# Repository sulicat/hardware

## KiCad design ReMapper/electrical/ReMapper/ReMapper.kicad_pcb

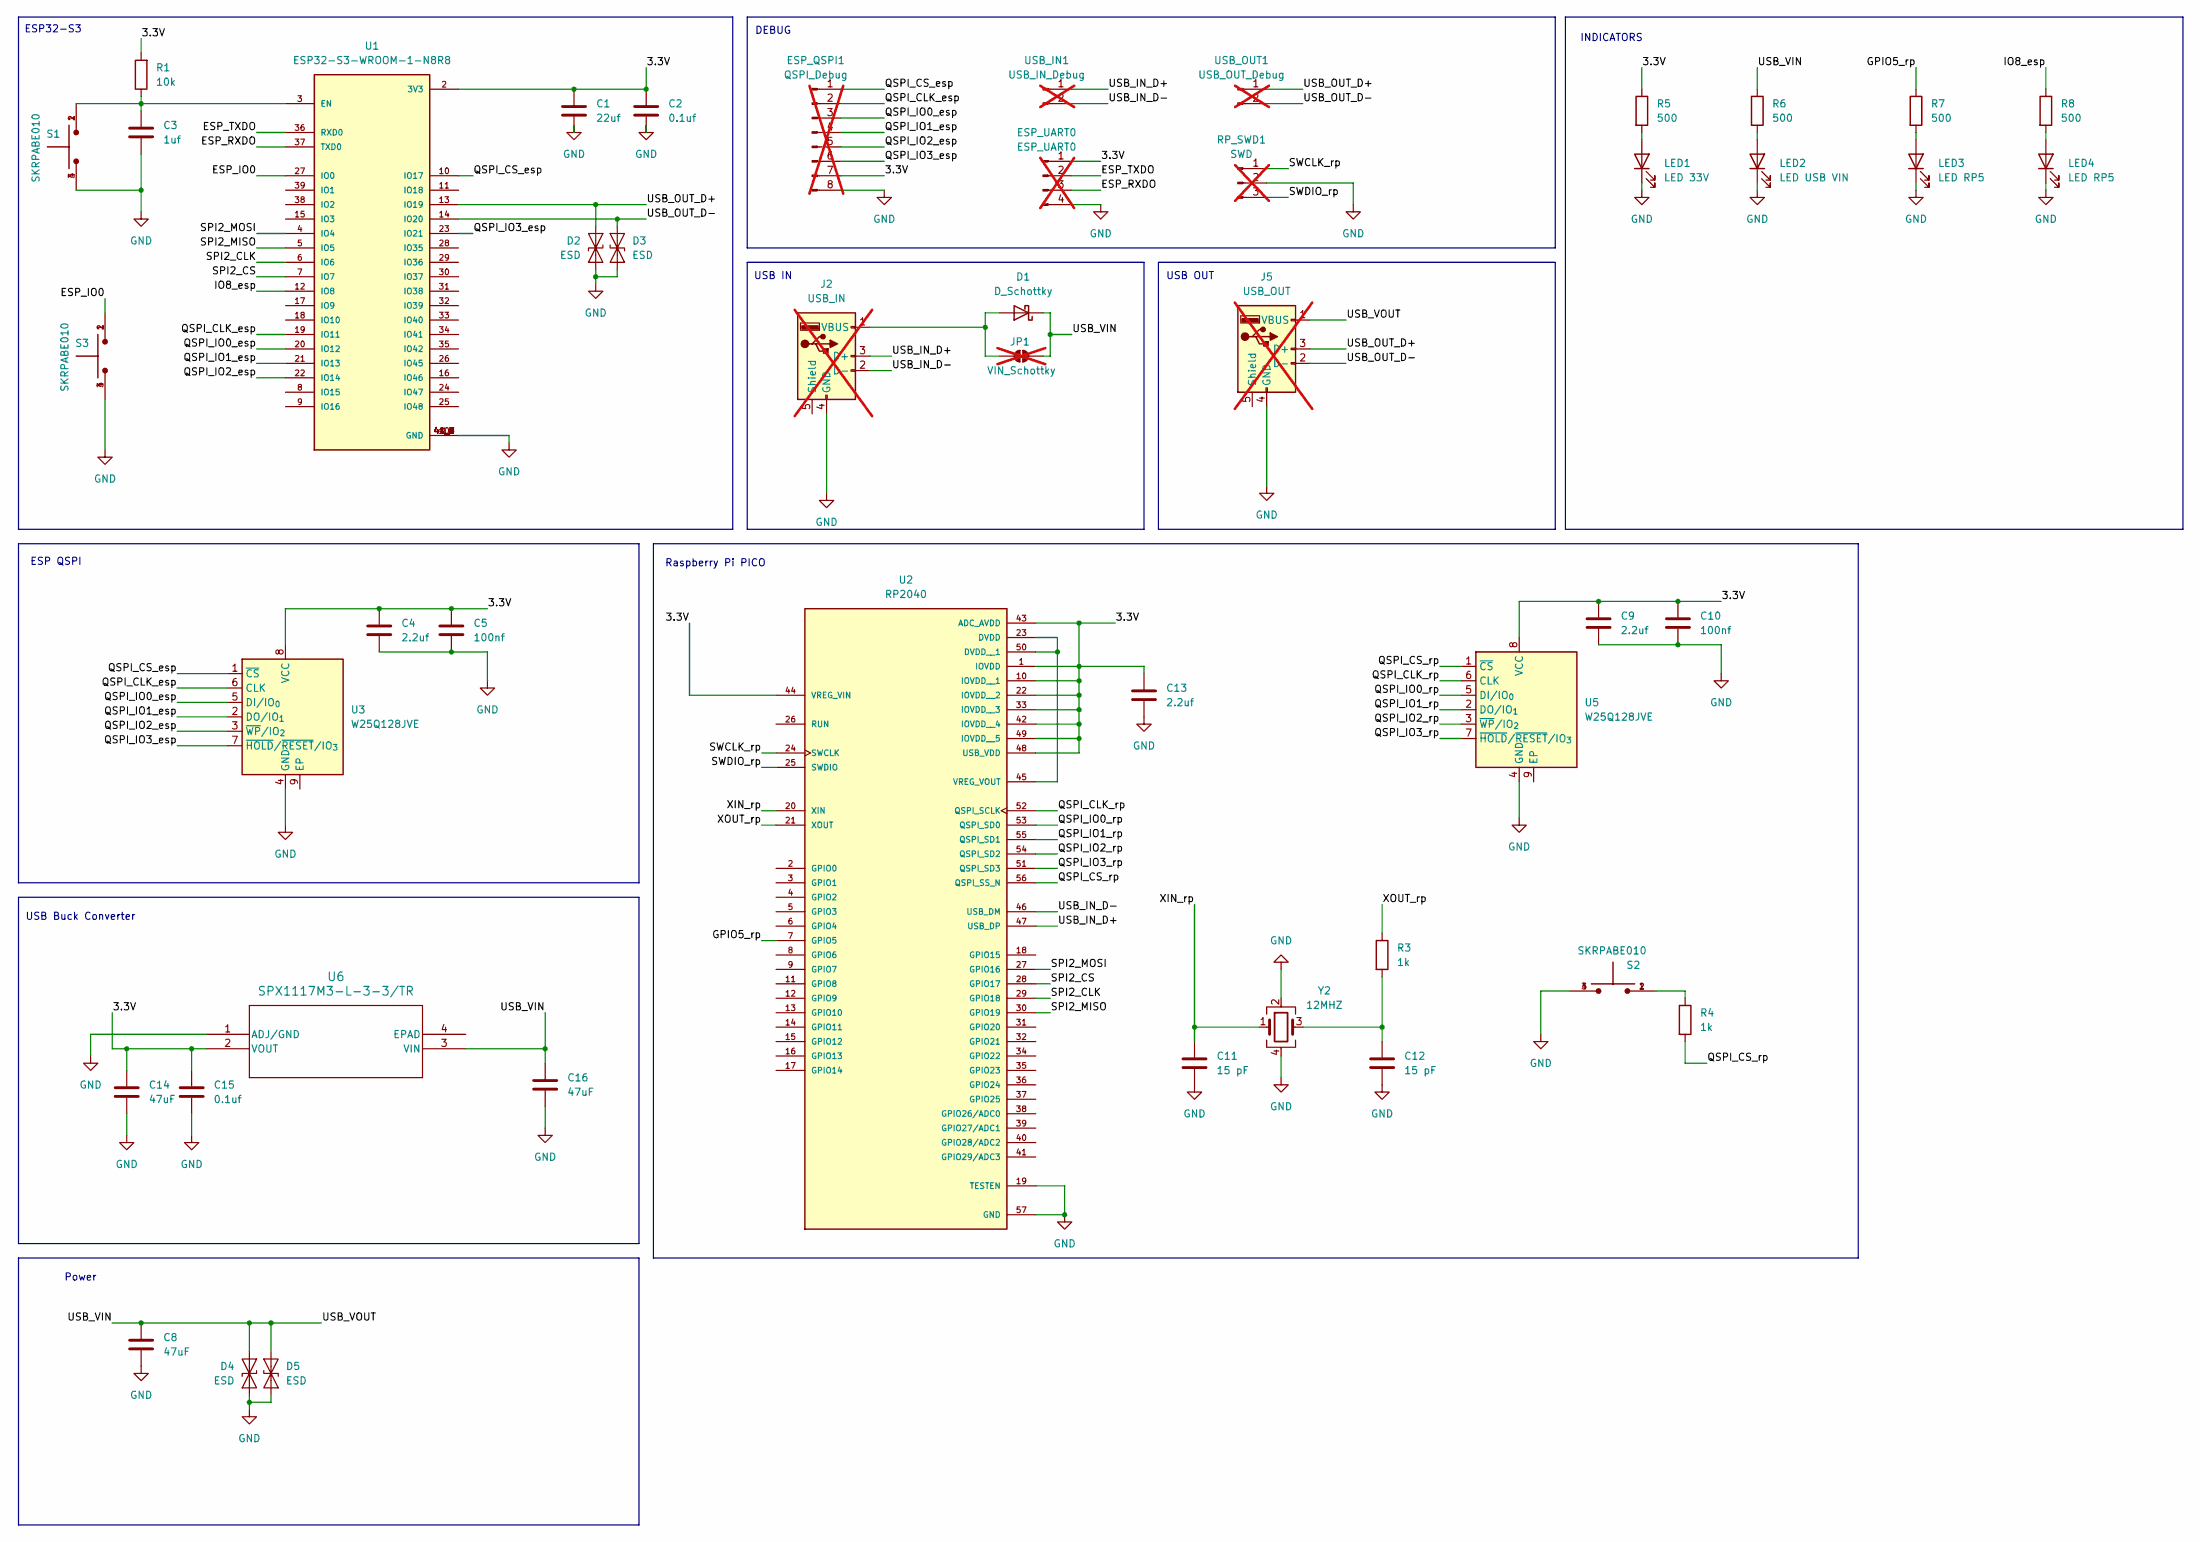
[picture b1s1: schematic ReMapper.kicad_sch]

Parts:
C1: 22uf; C_0603_1608Metric; LCSC Part C48579267
C2, C15: 0.1uf; C_0603_1608Metric; LCSC Part C14663
C3: 1uf; C_0603_1608Metric; LCSC Part C5189821
C4, C9, C13: 2.2uf; C_0603_1608Metric; LCSC Part C5189830
C5, C10: 100nf; C_0603_1608Metric; LCSC Part C5189821
C8, C14, C16: 47uF; C_0603_1608Metric; LCSC Part C140782
C11, C12: 15 pF; C_0603_1608Metric; LCSC Part C107037
D1: D_Schottky; D_SOD-123; LCSC Part C82544
D2, D3, D4, D5: ESD; D_SOD-523; LCSC Part SOD523
ESP_QSPI1: QSPI_Debug; PinHeader_1x08_P2.54mm_Vertical; not fitted
ESP_UART0: ESP_UART0; PinHeader_1x04_P2.54mm_Vertical; not fitted
J2: USB_IN; USBA_Female; not fitted
J5: USB_OUT; PinHeader_1x05_P2.54mm_Vertical; not fitted
JP1: VIN_Schottky; SolderJumper-2_P1.3mm_Open_Pad1.0x1.5mm; not fitted
LED1: LED 33V; LED_0603_1608Metric; LCSC Part C965807
LED2: LED USB VIN; LED_0603_1608Metric; LCSC Part C965807
LED3, LED4: LED RP5; LED_0603_1608Metric; LCSC Part C965807
R1: 10k; R_0603_1608Metric; LCSC Part C98220
R3, R4: 1k; R_0603_1608Metric; LCSC Part C22548
R5, R6, R7, R8: 500; R_0603_1608Metric; LCSC Part C860931
RP_SWD1: SWD; PinHeader_1x03_P2.54mm_Vertical; not fitted
S1, S2, S3: SKRPABE010; push_button_SKRPABE010; LCSC Part C115360
U1: ESP32-S3-WROOM-1-N8R8; XCVR_ESP32S3WROOM1N8R8; LCSC Part C2913201
U2: RP2040; rp2040; PARTREV 2.2; LCSC Part C2040
U3, U5: W25Q128JVE; WSON-8-1EP_8x6mm_P1.27mm_EP3.4x4.3mm; LCSC Part C401662
U6: SPX1117M3-L-3-3/TR; SOT-223; LCSC Part C6862
USB_IN1: USB_IN_Debug; PinHeader_1x02_P2.54mm_Vertical; not fitted
USB_OUT1: USB_OUT_Debug; PinHeader_1x02_P2.54mm_Vertical; not fitted
Y2: 12MHZ; Crystal_SMD_3225-4Pin_3.2x2.5mm; LCSC Part C9002

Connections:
/3.3V: C1.1, C2.1, C4.1, C5.1, C9.1, C10.1, C13.1, C14.1, C15.1, ESP_QSPI1.7, ESP_UART0.1, R1.2, R5.1, U1.2 (3V3), U2.1 (IOVDD), U2.10 (IOVDD__1), U2.22 (IOVDD__2), U2.33 (IOVDD__3), U2.42 (IOVDD__4), U2.43 (ADC_AVDD), U2.44 (VREG_VIN), U2.48 (USB_VDD), U2.49 (IOVDD__5), U3.8 (VCC), U5.8 (VCC), U6.2 (VOUT)
/ESP_IO0: S3.1, S3.2, U1.27 (IO0)
/ESP_RXDO: ESP_UART0.3, U1.37 (TXD0)
/ESP_TXDO: ESP_UART0.2, U1.36 (RXD0)
/GPIO5_rp: R7.1, U2.7 (GPIO5)
/IO8_esp: R8.1, U1.12 (IO8)
/QSPI_CLK_esp: ESP_QSPI1.2, U1.19 (IO11), U3.6 (CLK)
/QSPI_CLK_rp: U2.52 (QSPI_SCLK), U5.6 (CLK)
/QSPI_CS_esp: ESP_QSPI1.1, U1.10 (IO17), U3.1 (~CS)
/QSPI_CS_rp: R4.2, U2.56 (QSPI_SS_N), U5.1 (~CS)
/QSPI_IO0_esp: ESP_QSPI1.3, U1.20 (IO12), U3.5 (DI/IO_{0})
/QSPI_IO0_rp: U2.53 (QSPI_SD0), U5.5 (DI/IO_{0})
/QSPI_IO1_esp: ESP_QSPI1.4, U1.21 (IO13), U3.2 (DO/IO_{1})
/QSPI_IO1_rp: U2.55 (QSPI_SD1), U5.2 (DO/IO_{1})
/QSPI_IO2_esp: ESP_QSPI1.5, U1.22 (IO14), U3.3 (~WP/IO_{2})
/QSPI_IO2_rp: U2.54 (QSPI_SD2), U5.3 (~WP/IO_{2})
/QSPI_IO3_esp: ESP_QSPI1.6, U1.23 (IO21), U3.7 (~HOLD/~RESET/IO_{3})
/QSPI_IO3_rp: U2.51 (QSPI_SD3), U5.7 (~HOLD/~RESET/IO_{3})
/SPI2_CLK: U1.6 (IO6), U2.29 (GPIO18)
/SPI2_CS: U1.7 (IO7), U2.28 (GPIO17)
/SPI2_MISO: U1.5 (IO5), U2.30 (GPIO19)
/SPI2_MOSI: U1.4 (IO4), U2.27 (GPIO16)
/SWCLK_rp: RP_SWD1.1, U2.24 (SWCLK)
/SWDIO_rp: RP_SWD1.3, U2.25 (SWDIO)
/USB_IN_D+: J2.3 (D+), U2.47 (USB_DP), USB_IN1.1
/USB_IN_D-: J2.2 (D-), U2.46 (USB_DM), USB_IN1.2
/USB_OUT_D+: D2.1 (A1), J5.3 (D+), U1.13 (IO19), USB_OUT1.1
/USB_OUT_D-: D3.2 (A2), J5.2 (D-), U1.14 (IO20), USB_OUT1.2
/USB_VIN: C8.1, C16.1, D1.1 (K), D4.1 (A1), D5.2 (A2), J5.1 (VBUS), JP1.2 (B), R6.1, U6.3 (VIN)
/XIN_rp: C11.1, U2.20 (XIN), Y2.1
/XOUT_rp: R3.1, U2.21 (XOUT)
GND: C1.2, C2.2, C3.2, C4.2, C5.2, C8.2, C9.2, C10.2, C11.2, C12.2, C13.2, C14.2, C15.2, C16.2, D2.2 (A2), D3.1 (A1), D4.2 (A2), D5.1 (A1), ESP_QSPI1.8, ESP_UART0.4, J2.4 (GND), J5.4 (GND), LED1.1 (K), LED2.1 (K), LED3.1 (K), LED4.1 (K), RP_SWD1.2, S1.3, S1.4, S2.3, S2.4, S3.3, S3.4, U1.1 (GND), U1.40 (GND), U1.41_1 (GND), U1.41_2 (GND), U1.41_3 (GND), U1.41_4 (GND), U1.41_5 (GND), U1.41_6 (GND), U1.41_7 (GND), U1.41_8 (GND), U1.41_9 (GND), U2.19 (TESTEN), U2.57 (GND), U3.4 (GND), U5.4 (GND), U6.1 (ADJ/GND), Y2.2, Y2.4
unnamed: C12.1, R3.2, Y2.3
unnamed: D1.2 (A), J2.1 (VBUS), JP1.1 (A)
unnamed: LED1.2 (A), R5.2
unnamed: LED2.2 (A), R6.2
unnamed: LED3.2 (A), R7.2
unnamed: LED4.2 (A), R8.2
unnamed: R4.1, S2.1, S2.2
unnamed: C3.1, R1.1, S1.1, S1.2, U1.3 (EN)
unnamed: U2.23 (DVDD), U2.45 (VREG_VOUT), U2.50 (DVDD__1)

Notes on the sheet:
INDICATORS
USB IN
ESP QSPI
USB Buck Converter
Power
USB OUT
Raspberry Pi PICO
ESP32-S3
DEBUG

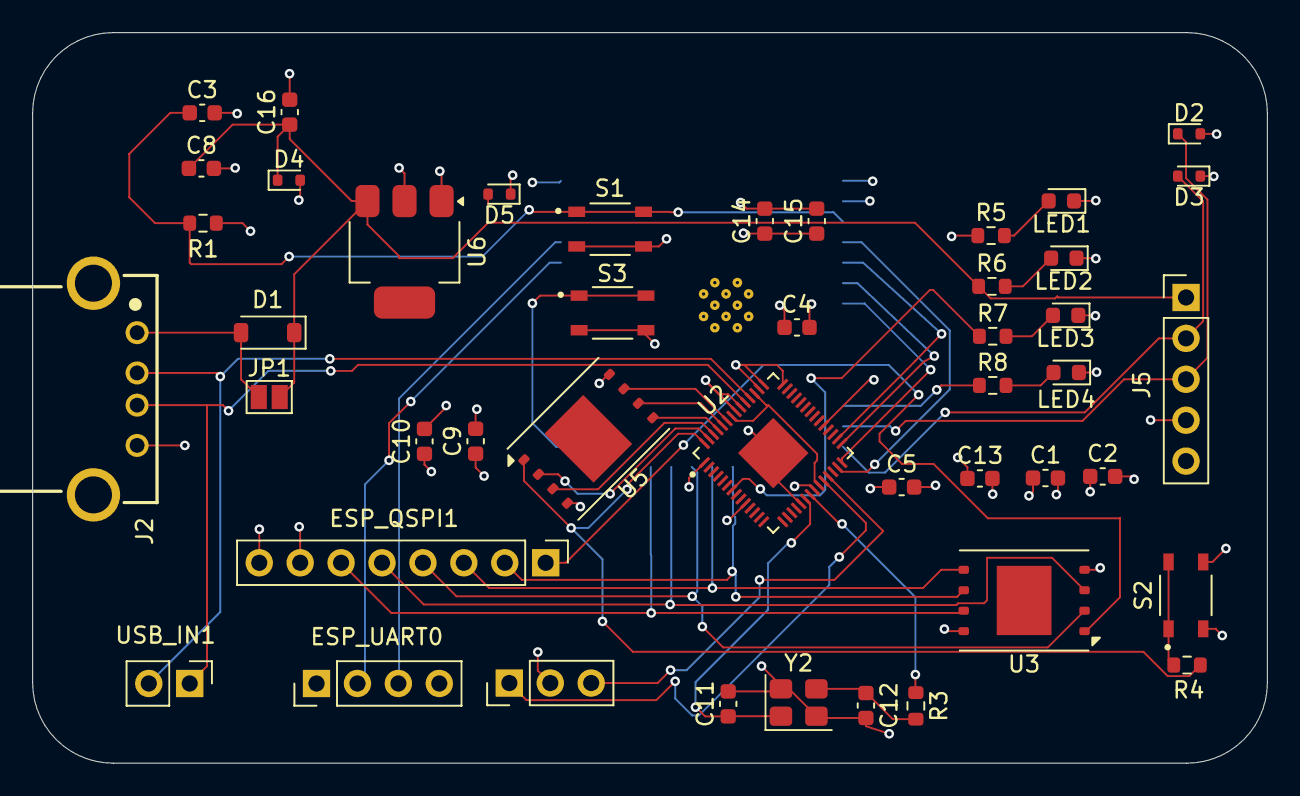
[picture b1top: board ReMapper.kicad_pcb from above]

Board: 4 copper layers, 76.7 x 45.3 mm, 46 parts (1 on the bottom side), 41 nets.

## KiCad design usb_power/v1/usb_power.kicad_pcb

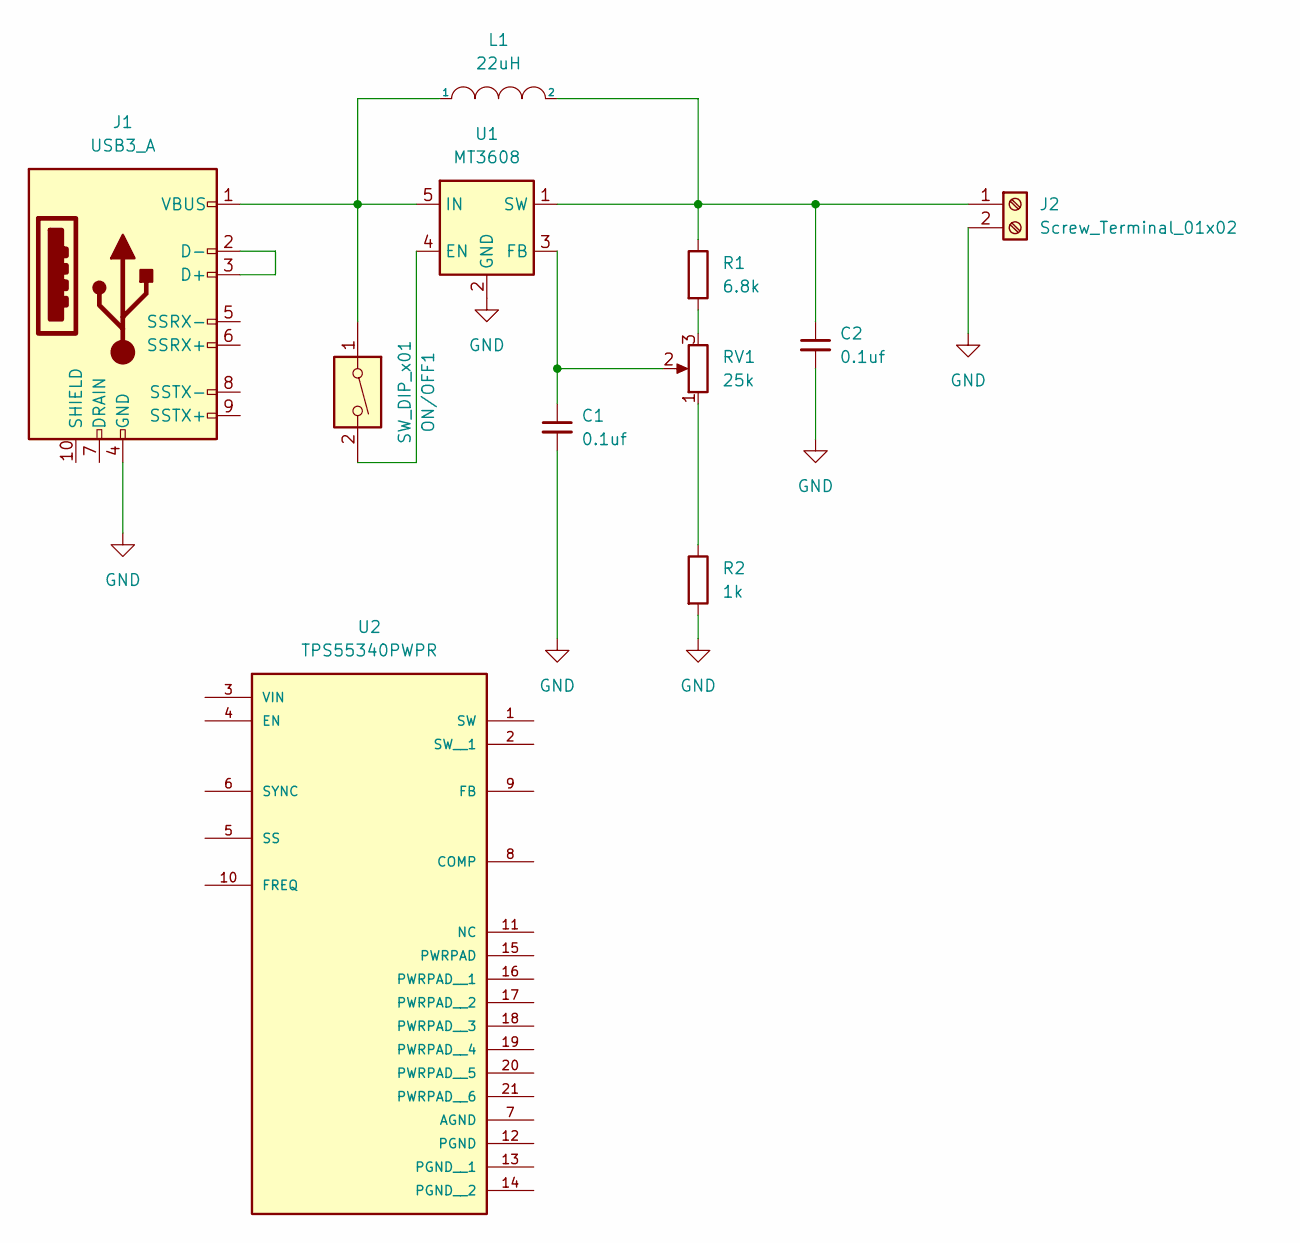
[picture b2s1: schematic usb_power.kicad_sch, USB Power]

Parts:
C1, C2: 0.1uf; CP_Elec_3x5.3
J1: USB3_A; USB3_MOLEX_0484050003; Part Number Digikey WM25179-ND
J2: Screw_Terminal_01x02; TerminalBlock_Phoenix_MKDS-1,5-2_1x02_P5.00mm_Horizontal
L1: 22uH; L_THT
ON/OFF1: SW_DIP_x01; SW_DS01_254-L-01BE_CUD
R1: 6.8k; R_0603_1608Metric
R2: 1k; R_0603_1608Metric
RV1: 25k; Potentiometer_Bourns_3339P_Vertical_HandSoldering
U1: MT3608; SOT-23-6; Part Number MT3608 SOT23-6
U2: TPS55340PWPR; IC_TPS55340PWPR; PARTREV E

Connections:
GND: C1.2, C2.2, J1.4 (GND), J2.2, R2.2, U1.2 (GND)
unnamed: J1.2 (D-), J1.3 (D+)
unnamed: J1.1 (VBUS), L1.1, ON/OFF1.1, U1.5 (IN)
unnamed: C2.1, J2.1, L1.2, R1.1, U1.1 (SW)
unnamed: R1.2, RV1.3
unnamed: R2.1, RV1.1
unnamed: ON/OFF1.2, U1.4 (EN)
unnamed: C1.1, RV1.2, U1.3 (FB)

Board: 2 copper layers, 11 parts (0 on the bottom side), 8 nets, no tracks yet.

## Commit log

2025-04-01 v1 usb power
2025-04-02 fail, this is hard!
2025-04-03 what a pain
2025-04-09 v1 pushed
2025-04-11 CH375B USB Breakout
2025-04-14 some basic code
2025-04-15 Basic HID output
2025-04-17 HT42B534
2025-05-01 renamed project
2025-05-01 added some datasheets
2025-05-01 new datasheets
2025-05-03 basic spi out from the esp32
2025-05-03 good pico cmake
2025-05-03 pico build process a little better
2025-05-03 some more rpi datasheets
2025-05-04 rpi spi master, need change to slave
2025-05-05 working spi comms
2025-05-05 more desirable pins
2025-05-06 uart via uart
2025-05-06 microsquirt
2025-05-06 io box microsquirt
2025-05-07 tusb on the pico
2025-05-07 removed notes
2025-05-08 fsusb data
2025-05-09 hid spec
2025-05-09 some basic 3D models
2025-05-20 getting device reports on pico
2025-05-21 HID report now forwarded via spi
2025-06-04 pushing before shifting to c++
2025-06-04 decoding HID message on the esp
2025-06-04 usb datasheet
2025-06-07 emulating gamepad now
2025-06-09 a little faster, 50mhz spi, but rp240 needs rethought
2025-06-09 much better. Keeping up with high speed USB now
2025-06-10 some minor cleanup
2025-06-13 added footprints
2025-06-13 started working real schamtic
2025-06-14 more work on schematic
2025-06-15 first draft schematic
2025-06-15 schematic first draft, onto layout
2025-06-15 started layout
2025-06-15 split he layout a little
2025-06-15 rough placements
2025-06-15 layout half done, might needs a remake
2025-06-18 passing DRC
2025-06-18 low lcsc inventory on some parts, switch to standard lib instead of extended for them. for the Crystal and Boost Convertor
2025-06-18 PDF of schematic
2025-06-18 added layout pdf
2025-06-18 better layout pdf
2025-06-19 picked basic parts from lcsc, pre fab
2025-06-19 V1 - Sent to FAb
2025-06-26 added io 8 blink and flash uart
2025-07-03 fixed up V1, added some debug. Now working on V2
2025-07-04 Remapper started V2 Layout
2025-07-04 started routing... not looking good, might start again
2025-07-04 trying to pass DRC
2025-07-08 V2 passing DRC
2025-07-08 schematic pdf
2025-07-09 added some silkscreen, sent V2 ReMapper to FAB
2025-07-11 soft wifi AP
2025-07-14 some side learning
2025-07-14 simple ADD/SUB ALU
2025-09-12 more datasheets
2025-11-08 orange pi
